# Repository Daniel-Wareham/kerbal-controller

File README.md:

# kerbal-controller
An Arduino custom controller for Kerbal Space Program

Read the project log for my process in building the controller
Read the technical explanation for explanations on both the software and hardware

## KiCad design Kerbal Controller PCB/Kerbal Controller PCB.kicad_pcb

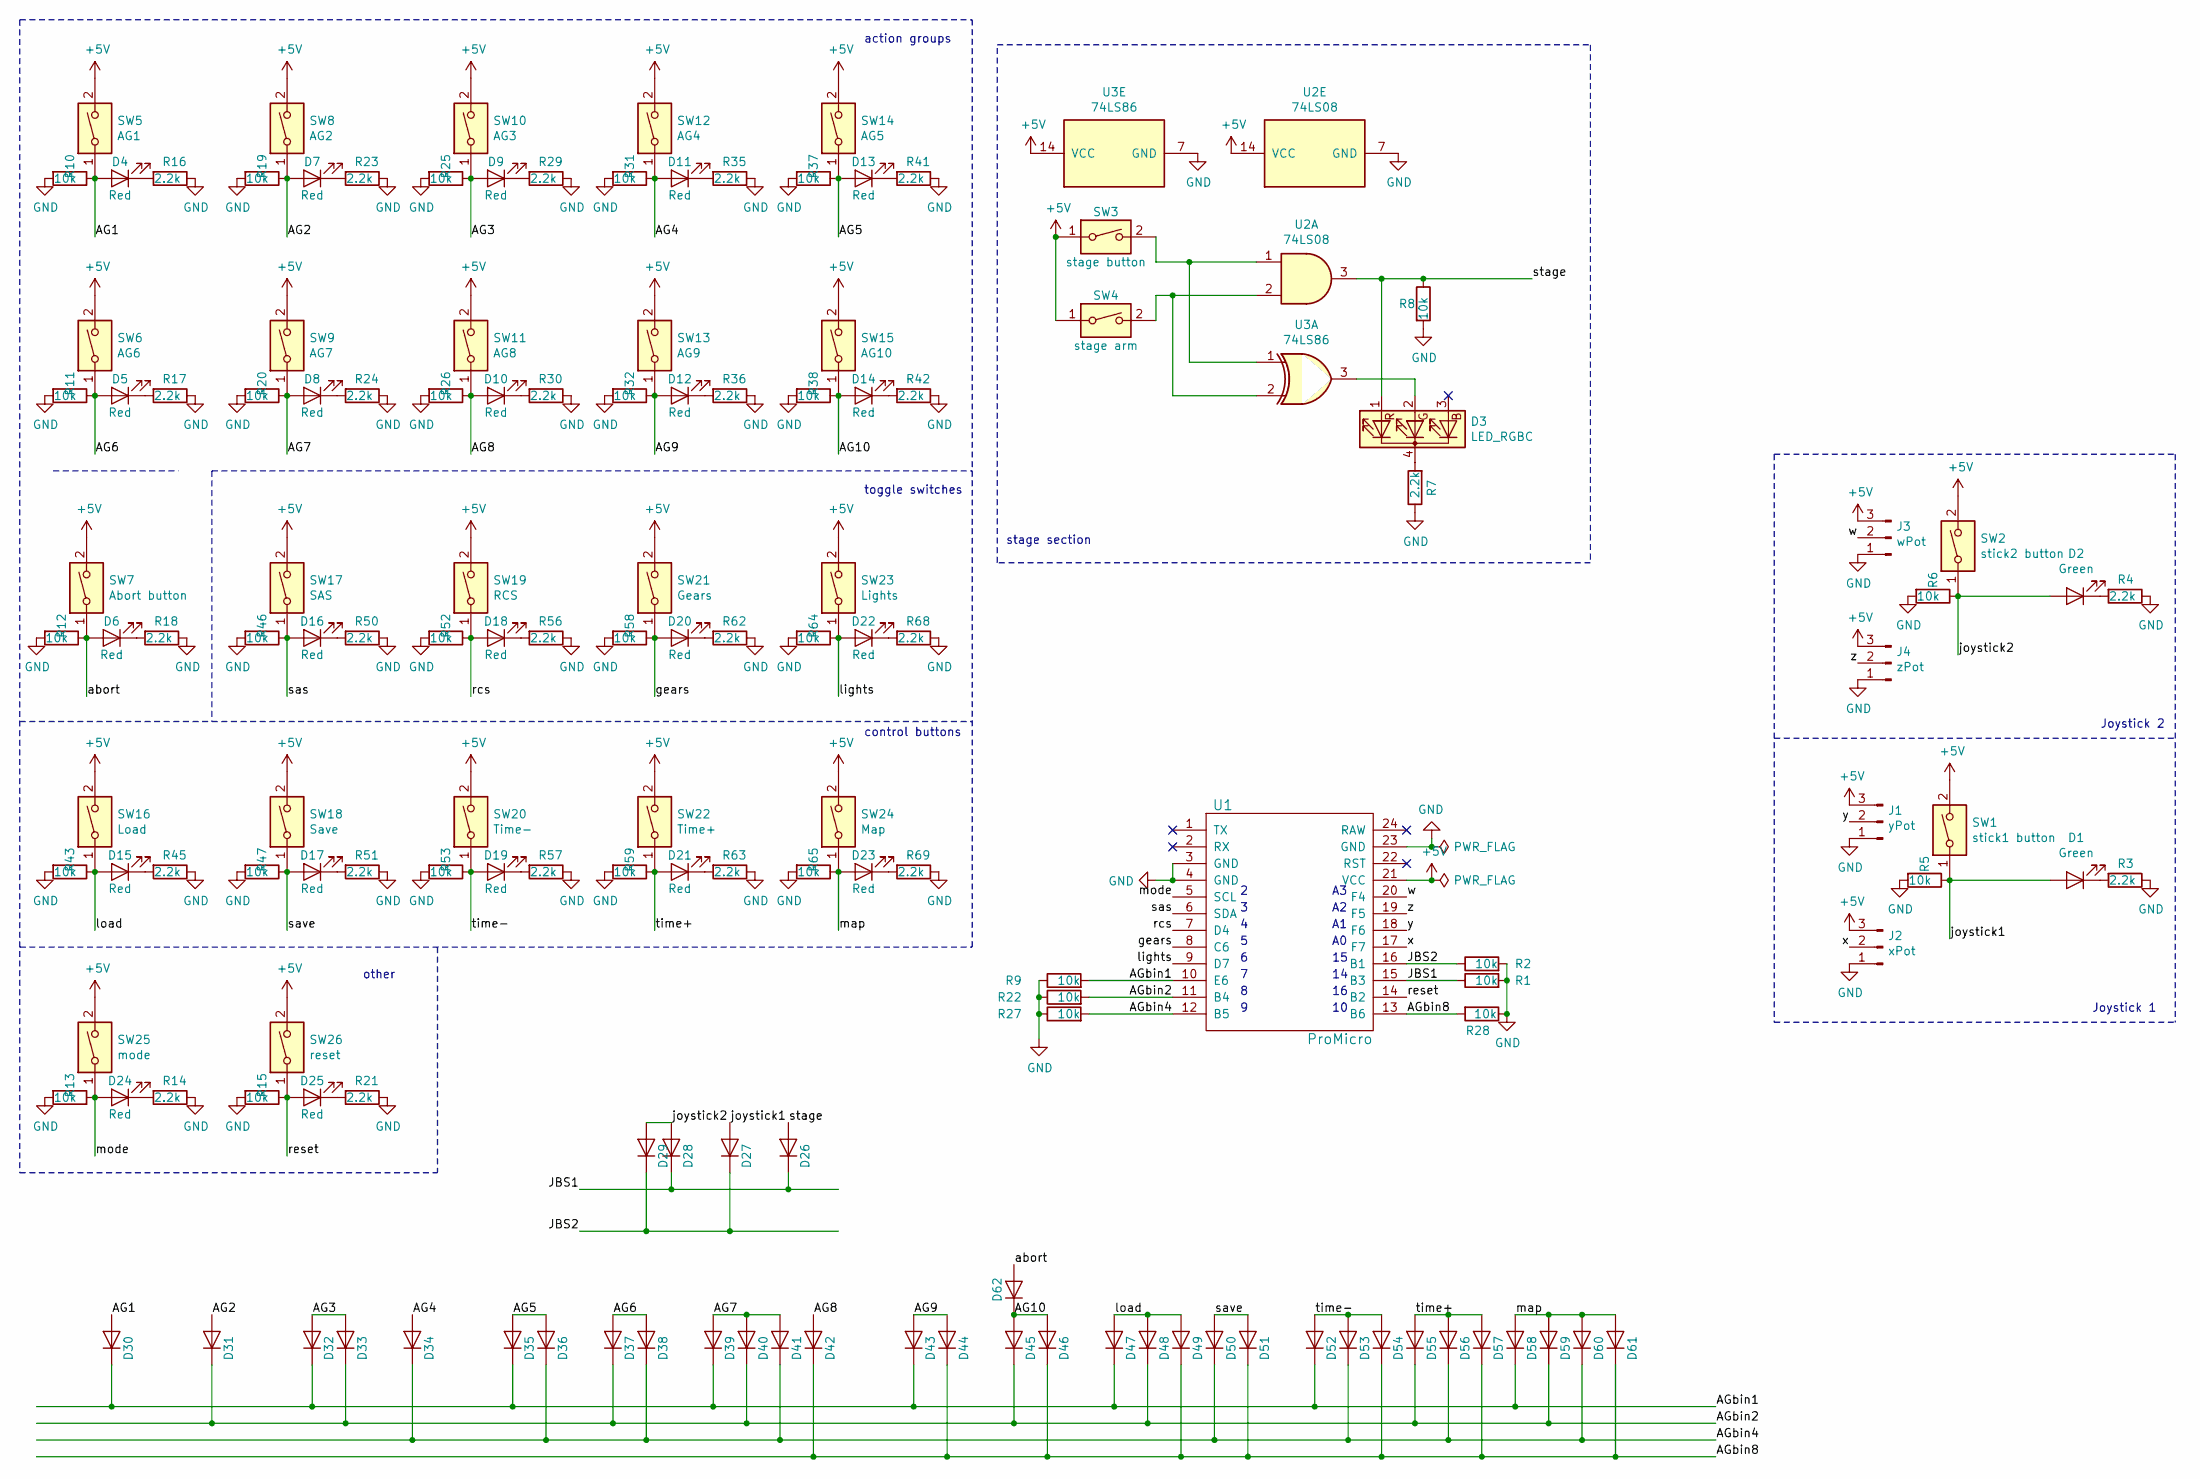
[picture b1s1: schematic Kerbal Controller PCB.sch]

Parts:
D1, D2: Green; LED_D5.0mm
D3: LED_RGBC; PinSocket_1x04_P2.54mm_Vertical
D4, D5, D6, D7, D8, D9, D10, D11, D12, D13, D14, D15, D16, D17, D18, D19, D20, D21, D22, D23, D24, D25: Red; LED_D5.0mm
D26, D27, D28, D29, D30, D31, D32, D33, D34, D35, D36, D37, D38, D39, D40, D41, D42, D43, D44, D45, D46, D47, D48, D49, D50, D51, D52, D53, D54, D55, D56, D57, D58, D59, D60, D61, D62: D; D_A-405_P7.62mm_Horizontal
J1: yPot; PinHeader_1x03_P2.54mm_Vertical
J2: xPot; PinHeader_1x03_P2.54mm_Vertical
J3: wPot; PinHeader_1x03_P2.54mm_Vertical
J4: zPot; PinHeader_1x03_P2.54mm_Vertical
R1, R2, R5, R6, R8, R9, R10, R11, R12, R13, R15, R19, R20, R22, R25, R26, R27, R28, R31, R32, R37, R38, R43, R46, R47, R52, R53, R58, R59, R64, R65: 10k; R_Axial_DIN0207_L6.3mm_D2.5mm_P7.62mm_Horizontal
R3, R4, R7, R14, R16, R17, R18, R21, R23, R24, R29, R30, R35, R36, R41, R42, R45, R50, R51, R56, R57, R62, R63, R68, R69: 2.2k; R_Axial_DIN0207_L6.3mm_D2.5mm_P7.62mm_Horizontal
SW1: stick1 button; PinHeader_1x02_P2.54mm_Vertical
SW2: stick2 button; PinHeader_1x02_P2.54mm_Vertical
SW3: stage button; PinHeader_1x02_P2.54mm_Vertical
SW4: stage arm; PinHeader_1x02_P2.54mm_Vertical
SW5: AG1; PinHeader_1x02_P2.54mm_Vertical
SW6: AG6; PinHeader_1x02_P2.54mm_Vertical
SW7: Abort button; PinHeader_1x02_P2.54mm_Vertical
SW8: AG2; PinHeader_1x02_P2.54mm_Vertical
SW9: AG7; PinHeader_1x02_P2.54mm_Vertical
SW10: AG3; PinHeader_1x02_P2.54mm_Vertical
SW11: AG8; PinHeader_1x02_P2.54mm_Vertical
SW12: AG4; PinHeader_1x02_P2.54mm_Vertical
SW13: AG9; PinHeader_1x02_P2.54mm_Vertical
SW14: AG5; PinHeader_1x02_P2.54mm_Vertical
SW15: AG10; PinHeader_1x02_P2.54mm_Vertical
SW16: Load; PinHeader_1x02_P2.54mm_Vertical
SW17: SAS; PinHeader_1x02_P2.54mm_Vertical
SW18: Save; PinHeader_1x02_P2.54mm_Vertical
SW19: RCS; PinHeader_1x02_P2.54mm_Vertical
SW20: Time-; PinHeader_1x02_P2.54mm_Vertical
SW21: Gears; PinHeader_1x02_P2.54mm_Vertical
SW22: Time+; PinHeader_1x02_P2.54mm_Vertical
SW23: Lights; PinHeader_1x02_P2.54mm_Vertical
SW24: Map; PinHeader_1x02_P2.54mm_Vertical
SW25: mode; PinHeader_1x02_P2.54mm_Vertical
SW26: reset; PinHeader_1x02_P2.54mm_Vertical
U1: ProMicro
U2: 74LS08; DIP-14_W7.62mm_LongPads
U3: 74LS86; DIP-14_W7.62mm_LongPads

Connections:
+5V: J1.3, J2.3, J3.3, J4.3, SW1.2, SW2.2, SW3.1, SW4.1, SW5.2, SW6.2, SW7.2, SW8.2, SW9.2, SW10.2, SW11.2, SW12.2, SW13.2, SW14.2, SW15.2, SW16.2, SW17.2, SW18.2, SW19.2, SW20.2, SW21.2, SW22.2, SW23.2, SW24.2, SW25.2, SW26.2, U1.21 (VCC), U2.14 (VCC), U3.14 (VCC)
/AG1: D4.2 (A), D30.2 (A), R10.1, SW5.1
/AG2: D7.2 (A), D31.2 (A), R19.1, SW8.1
/AG3: D9.2 (A), D32.2 (A), D33.2 (A), R25.1, SW10.1
/AG4: D11.2 (A), D34.2 (A), R31.1, SW12.1
/AG5: D13.2 (A), D35.2 (A), D36.2 (A), R37.1, SW14.1
/AG6: D5.2 (A), D37.2 (A), D38.2 (A), R11.1, SW6.1
/AG7: D8.2 (A), D39.2 (A), D40.2 (A), D41.2 (A), R20.1, SW9.1
/AG8: D10.2 (A), D42.2 (A), R26.1, SW11.1
/AG9: D12.2 (A), D43.2 (A), D44.2 (A), R32.1, SW13.1
/AG10: D14.2 (A), D45.2 (A), D46.2 (A), D62.1 (K), R38.1, SW15.1
/AGbin1: D30.1 (K), D32.1 (K), D35.1 (K), D39.1 (K), D43.1 (K), D47.1 (K), D52.1 (K), D58.1 (K), R9.2, U1.10 (E6)
/AGbin2: D31.1 (K), D33.1 (K), D37.1 (K), D40.1 (K), D45.1 (K), D48.1 (K), D55.1 (K), D59.1 (K), R22.2, U1.11 (B4)
/AGbin4: D34.1 (K), D36.1 (K), D38.1 (K), D41.1 (K), D50.1 (K), D53.1 (K), D56.1 (K), D60.1 (K), R27.2, U1.12 (B5)
/AGbin8: D42.1 (K), D44.1 (K), D46.1 (K), D49.1 (K), D51.1 (K), D54.1 (K), D57.1 (K), D61.1 (K), R28.2, U1.13 (B6)
/JBS1: D26.1 (K), D28.1 (K), R1.1, U1.15 (B3)
/JBS2: D27.1 (K), D29.1 (K), R2.1, U1.16 (B1)
/abort: D6.2 (A), D62.2 (A), R12.1, SW7.1
/gears: D20.2 (A), R58.1, SW21.1, U1.8 (C6)
/joystick1: D1.2 (A), D27.2 (A), R5.1, SW1.1
/joystick2: D2.2 (A), D28.2 (A), D29.2 (A), R6.1, SW2.1
/lights: D22.2 (A), R64.1, SW23.1, U1.9 (D7)
/load: D15.2 (A), D47.2 (A), D48.2 (A), D49.2 (A), R43.1, SW16.1
/map: D23.2 (A), D58.2 (A), D59.2 (A), D60.2 (A), D61.2 (A), R65.1, SW24.1
/mode: D24.2 (A), R13.1, SW25.1, U1.5 (SCL)
/rcs: D18.2 (A), R52.1, SW19.1, U1.7 (D4)
/reset: D25.2 (A), R15.1, SW26.1, U1.14 (B2)
/sas: D16.2 (A), R46.1, SW17.1, U1.6 (SDA)
/save: D17.2 (A), D50.2 (A), D51.2 (A), R47.1, SW18.1
/stage: D3.1 (RA), D26.2 (A), R8.1, U2.3
/time+: D21.2 (A), D55.2 (A), D56.2 (A), D57.2 (A), R59.1, SW22.1
/time-: D19.2 (A), D52.2 (A), D53.2 (A), D54.2 (A), R53.1, SW20.1
/w: J3.2, U1.20 (F4)
/x: J2.2, U1.17 (F7)
/y: J1.2, U1.18 (F6)
/z: J4.2, U1.19 (F5)
GND: J1.1, J2.1, J3.1, J4.1, R1.2, R2.2, R3.1, R4.1, R5.2, R6.2, R7.1, R8.2, R9.1, R10.2, R11.2, R12.2, R13.2, R14.1, R15.2, R16.1, R17.1, R18.1, R19.2, R20.2, R21.1, R22.1, R23.1, R24.1, R25.2, R26.2, R27.1, R28.1, R29.1, R30.1, R31.2, R32.2, R35.1, R36.1, R37.2, R38.2, R41.1, R42.1, R43.2, R45.1, R46.2, R47.2, R50.1, R51.1, R52.2, R53.2, R56.1, R57.1, R58.2, R59.2, R62.1, R63.1, R64.2, R65.2, R68.1, R69.1, U1.3 (GND), U1.4 (GND), U1.23 (GND), U2.7 (GND), U3.7 (GND)
unnamed: D1.1 (K), R3.2
unnamed: D2.1 (K), R4.2
unnamed: D3.2 (GA), U3.3
unnamed: D3.4 (K), R7.2
unnamed: D4.1 (K), R16.2
unnamed: D5.1 (K), R17.2
unnamed: D6.1 (K), R18.2
unnamed: D7.1 (K), R23.2
unnamed: D8.1 (K), R24.2
unnamed: D9.1 (K), R29.2
unnamed: D10.1 (K), R30.2
unnamed: D11.1 (K), R35.2
unnamed: D12.1 (K), R36.2
unnamed: D13.1 (K), R41.2
unnamed: D14.1 (K), R42.2
unnamed: D15.1 (K), R45.2
unnamed: D16.1 (K), R50.2
unnamed: D17.1 (K), R51.2
unnamed: D18.1 (K), R56.2
unnamed: D19.1 (K), R57.2
unnamed: D20.1 (K), R62.2
unnamed: D21.1 (K), R63.2
unnamed: D22.1 (K), R68.2
unnamed: D23.1 (K), R69.2
unnamed: D24.1 (K), R14.2
unnamed: D25.1 (K), R21.2
unnamed: SW3.2, U2.1, U3.1
unnamed: SW4.2, U2.2, U3.2

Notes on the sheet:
Joystick 2
Joystick 1
stage section
action groups
toggle switches
control buttons
other

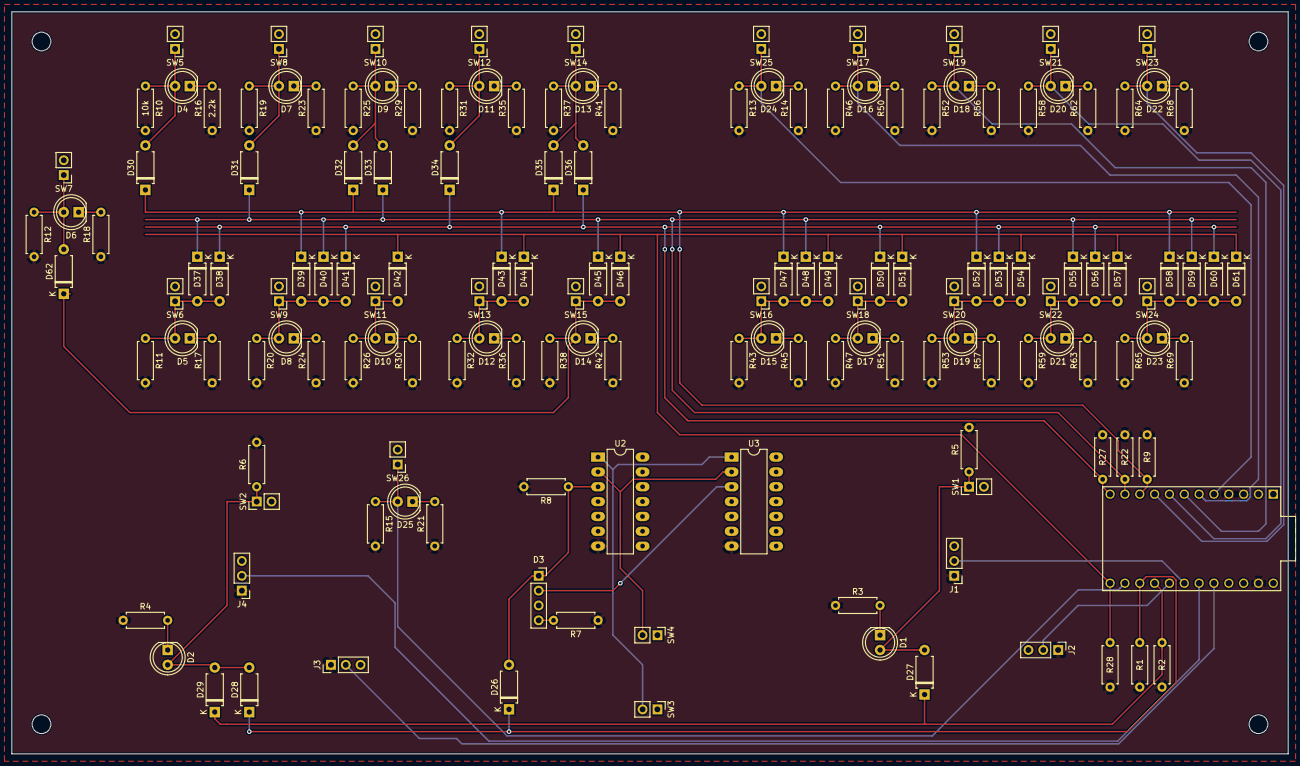
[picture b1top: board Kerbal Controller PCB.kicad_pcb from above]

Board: 2 copper layers, 218.4 x 127.0 mm, 151 parts (0 on the bottom side), 65 nets.
